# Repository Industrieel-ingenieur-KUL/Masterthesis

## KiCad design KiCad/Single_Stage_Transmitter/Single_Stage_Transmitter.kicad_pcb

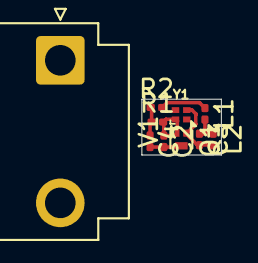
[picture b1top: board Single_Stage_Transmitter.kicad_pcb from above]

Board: 2 copper layers, 4.4 x 3.1 mm, 10 parts (0 on the bottom side), 6 nets.

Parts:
C2: 5p; C_0201_0603Metric
C3: 6p; C_0201_0603Metric
C4: 580n; C_0201_0603Metric
L1: 200n; L_0201_0603Metric
L2: 298n; L_0201_0603Metric
Q1: QRF; Diodes_DFN1006-3
R1: 50k; R_0201_0603Metric
R2: 200k; R_0201_0603Metric
V1: 3; JST_VH_B2P3-VH_1x02_P7.92mm_Vertical
Y1: Crystal; ABM14N800000MHZ8N1V

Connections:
0: C2.2, C4.2, Q1.3 (E), V1.2
/Base: C2.1, Q1.2 (B), R1.2, Y1.1
/Collector: C3.2, L2.2, Q1.1 (C), Y1.3
/OUT: C3.1, L1.2, L2.1
/Vcc: L1.1, R2.2, V1.1
unnamed: C4.1, R1.1, R2.1

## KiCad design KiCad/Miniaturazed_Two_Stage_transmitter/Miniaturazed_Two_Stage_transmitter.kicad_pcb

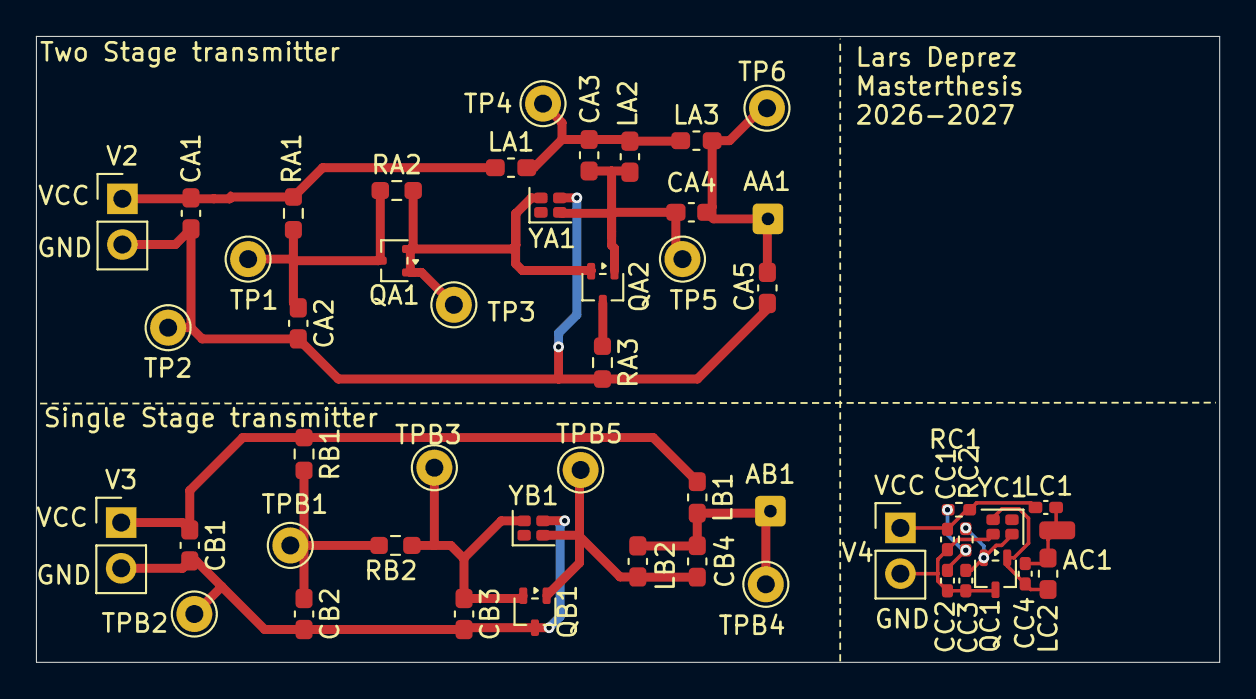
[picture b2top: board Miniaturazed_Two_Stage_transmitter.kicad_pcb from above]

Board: 2 copper layers, 65.7 x 34.8 mm, 51 parts (0 on the bottom side), 20 nets.

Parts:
AA1: Antenna; SolderWire-0.127sqmm_1x01_D0.48mm_OD1mm
AB1: Antenna; SolderWire-0.127sqmm_1x01_D0.48mm_OD1mm
AC1: Antenna; SolderWirePad_1x01_SMD_1x2mm
CA1: 220n; C_0603_1608Metric_Pad1.08x0.95mm_HandSolder
CA2: 580n; C_0603_1608Metric_Pad1.08x0.95mm_HandSolder
CA3: 15p; C_0603_1608Metric_Pad1.08x0.95mm_HandSolder
CA4: 3.3p; C_0603_1608Metric_Pad1.08x0.95mm_HandSolder
CA5: 2.2p; C_0603_1608Metric_Pad1.08x0.95mm_HandSolder
CB1: 100n; C_0603_1608Metric_Pad1.08x0.95mm_HandSolder
CB2: 580n; C_0603_1608Metric_Pad1.08x0.95mm_HandSolder
CB3, CB4: 15p; C_0603_1608Metric_Pad1.08x0.95mm_HandSolder
CC1: 100n; C_0402_1005Metric_Pad0.74x0.62mm_HandSolder
CC2: 580n; C_0402_1005Metric_Pad0.74x0.62mm_HandSolder
CC3, CC4: 15p; C_0402_1005Metric_Pad0.74x0.62mm_HandSolder
LA1, LA3: 100n; L_0603_1608Metric_Pad1.05x0.95mm_HandSolder
LA2: 1u; L_0603_1608Metric_Pad1.05x0.95mm_HandSolder
LB1: 82n; L_0603_1608Metric_Pad1.05x0.95mm_HandSolder
LB2: 1u; L_0603_1608Metric_Pad1.05x0.95mm_HandSolder
LC1: 82n; L_0402_1005Metric_Pad0.77x0.64mm_HandSolder
LC2: 1u; L_0603_1608Metric_Pad1.05x0.95mm_HandSolder
QA1: PDTA114; SOT-323_SC-70
QA2: NPN; SOT-323_SC-70
QB1: NPN; SOT-323_SC-70
QC1: NPN; SOT-323_SC-70
RA1: 2.2Meg; R_0603_1608Metric_Pad0.98x0.95mm_HandSolder
RA2: 15k; R_0603_1608Metric_Pad0.98x0.95mm_HandSolder
RA3: 58; R_0603_1608Metric_Pad0.98x0.95mm_HandSolder
RB1: 2.2Meg; R_0603_1608Metric_Pad0.98x0.95mm_HandSolder
RB2: 390k; R_0603_1608Metric_Pad0.98x0.95mm_HandSolder
RC1: 2.2Meg; R_0402_1005Metric_Pad0.72x0.64mm_HandSolder
RC2: 390k; R_0402_1005Metric_Pad0.72x0.64mm_HandSolder
TP1: Pulse_s1; Pin_D1.0mm_L10.0mm
TP2: GND; Pin_D1.0mm_L10.0mm
TP3: B_Q1; Pin_D1.0mm_L10.0mm
TP4: match_net; Pin_D1.0mm_L10.0mm
TP5: C_Q1; Pin_D1.0mm_L10.0mm
TP6: Output; Pin_D1.0mm_L10.0mm
TPB1: RC; Pin_D1.0mm_L10.0mm
TPB2: GND; Pin_D1.0mm_L10.0mm
TPB3: Q1_B; Pin_D1.0mm_L10.0mm
TPB4: RF; Pin_D1.0mm_L10.0mm
TPB5: Q1_C; Pin_D1.0mm_L10.0mm
V2, V3, V4: 3; PinHeader_1x02_P2.54mm_Vertical
YA1: Crystal; Crystal_SMD_WE_IQXC-26-4Pin_1.6x1.2mm
YB1: Crystal; Crystal_SMD_WE_IQXC-26-4Pin_1.6x1.2mm
YC1: Crystal; Crystal_SMD_WE_IQXC-26-4Pin_1.6x1.2mm

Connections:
/Full/GNDA: CA1.2, CA2.2, CA5.2, RA3.2, TP2.1 (1_1), V2.2, YA1.3
/Full/OUT: AA1.1 (A_1), CA4.1, CA5.1, LA3.2, TP6.1 (1_1)
/Single_stage_transmitter/GNDB: CB1.2, CB2.2, CB3.2, QB1.3 (E), TPB2.1 (1_1), V3.2, YB1.3
/Single_stage_transmitter/GNDC: CC1.2, CC2.2, CC3.2, QC1.3 (E), V4.2, YC1.3
/Single_stage_transmitter/RC: CB2.1, RB1.2, RB2.1, TPB1.1 (1_1)
/Single_stage_transmitter/RCB: CC2.1, RC1.2, RC2.1
/Single_stage_transmitter/RF: AB1.1 (A_1), CB4.2, LB1.2, LB2.1, TPB4.1 (1_1)
/Single_stage_transmitter/RFB: AC1.1 (A_1), CC4.2, LC1.2, LC2.1
unnamed: CA1.1, LA1.1, RA1.1, V2.1
unnamed: CA3.2, LA1.2, LA2.1, LA3.1, TP4.1 (1_1)
unnamed: CB1.1, LB1.1, RB1.1, V3.1
unnamed: CC1.1, LC1.1, RC1.1, V4.1
unnamed: QA1.1 (C), QA1.2 (B), QA2.2 (B), RA2.2, TP3.1 (1_1), YA1.4
unnamed: CA2.1, QA1.3 (E), RA1.2, RA2.1, TP1.1 (1_1)
unnamed: CA3.1, CA4.2, LA2.2, QA2.1 (C), TP5.1 (1_1), YA1.2
unnamed: QA2.3 (E), RA3.1
unnamed: CB3.1, QB1.2 (B), RB2.2, TPB3.1 (1_1), YB1.4
unnamed: CB4.1, LB2.2, QB1.1 (C), TPB5.1 (1_1), YB1.2
unnamed: CC3.1, QC1.2 (B), RC2.2, YC1.4
unnamed: CC4.1, LC2.2, QC1.1 (C), YC1.2
